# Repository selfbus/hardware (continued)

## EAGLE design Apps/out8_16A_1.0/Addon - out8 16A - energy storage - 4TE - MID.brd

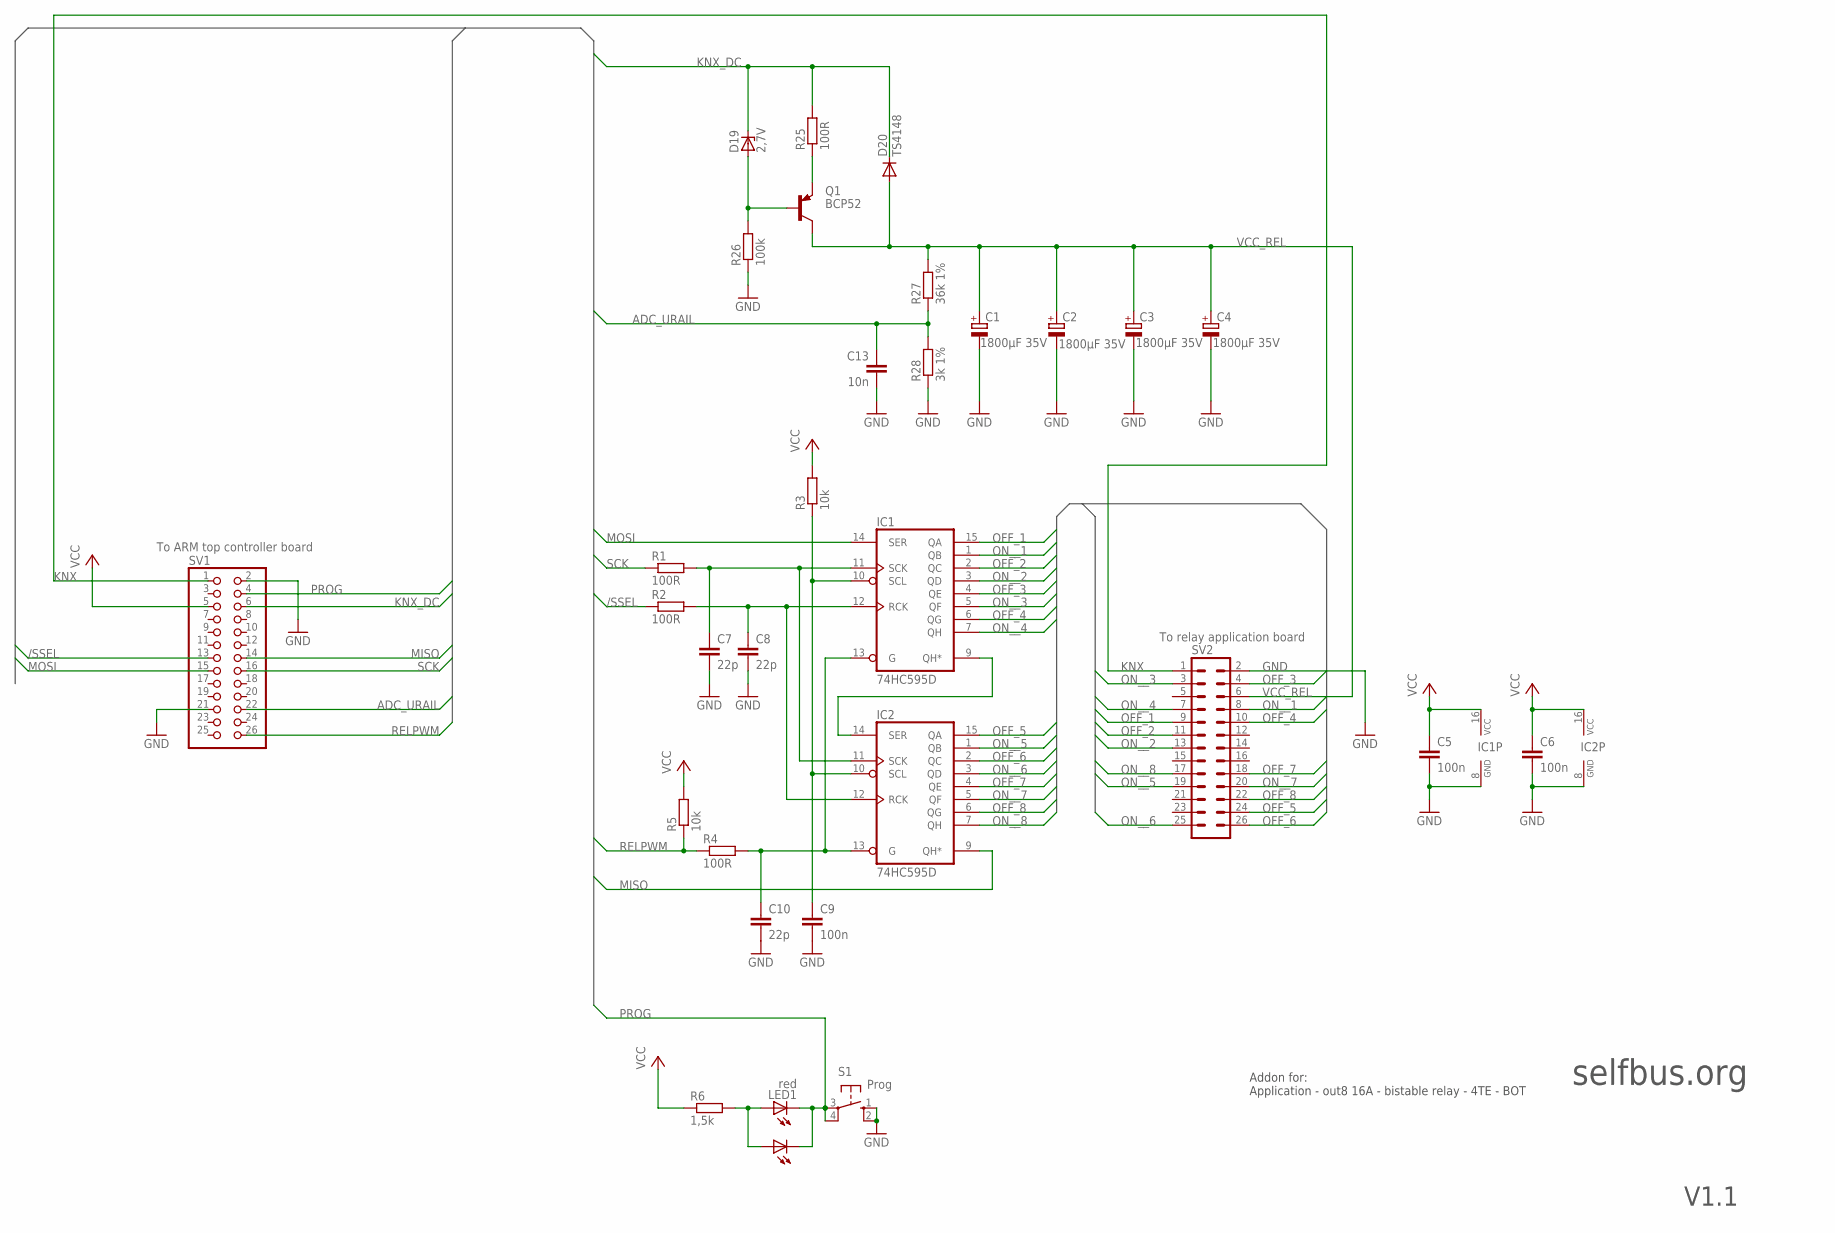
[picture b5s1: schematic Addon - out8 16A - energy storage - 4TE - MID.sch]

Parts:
C1, C2, C3, C4: 1800µF 35V; E5-13-30
C5, C6, C9: 100n; R0805M
C7, C8, C10: 22p; R0805M
C13: 10n; R0805M
D19: 2,7V; SOT23
D20: TS4148; D0805
IC1, IC2: 74HC595D; SO16
LED1: red; LED3MM
LED2: LG_T679-E1F1-1; PLCC2
Q1: BCP52; SOT223
R1, R2, R4, R25: 100R; R0805M
R3, R5: 10k; R0805M
R6: 1,5k; R0805M
R26: 100k; R0805M
R27: 36k 1%; R0805M
R28: 3k 1%; R0805M
S1: Prog; B3F-10XX
SV1: B; 2X13SMD
SV2: A; ML26

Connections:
/SSEL: R2.1, SV1.13
ADC_URAIL: C13.1, R27.1, R28.2, SV1.22
GND: C1.-, C2.-, C3.-, C4.-, C5.2, C6.2, C7.2, C8.2, C9.2, C10.2, C13.2, IC1.8 (GND), IC2.8 (GND), R26.1, R28.1, S1.1 (S), S1.2 (S1), SV1.2, SV1.21, SV2.2
KNX: SV1.1, SV2.1
KNX_DC: D19.3 (C), D20.C, R25.2, SV1.6
MISO: IC2.9 (QH*), SV1.14
MOSI: IC1.14 (SER), SV1.15
unnamed: D19.1 (A), Q1.1 (B), R26.2
unnamed: IC1.9 (QH*), IC2.14 (SER)
unnamed: C7.1, IC1.11 (SCK), IC2.11 (SCK), R1.2
unnamed: C8.1, IC1.12 (RCK), IC2.12 (RCK), R2.2
unnamed: LED1.A, LED2.A, R6.2
unnamed: Q1.3 (E), R25.1
unnamed: C10.1, IC1.13 (G), IC2.13 (G), R4.2
unnamed: C9.1, IC1.10 (SCL), IC2.10 (SCL), R3.1
OFF_1: IC1.15 (QA), SV2.9
OFF_2: IC1.2 (QC), SV2.11
OFF_3: IC1.4 (QE), SV2.4
OFF_4: IC1.6 (QG), SV2.10
OFF_5: IC2.15 (QA), SV2.24
OFF_6: IC2.2 (QC), SV2.26
OFF_7: IC2.4 (QE), SV2.18
OFF_8: IC2.6 (QG), SV2.22
ON__1: IC1.1 (QB), SV2.8
ON__2: IC1.3 (QD), SV2.13
ON__3: IC1.5 (QF), SV2.3
ON__4: IC1.7 (QH), SV2.7
ON__5: IC2.1 (QB), SV2.19
ON__6: IC2.3 (QD), SV2.25
ON__7: IC2.5 (QF), SV2.20
ON__8: IC2.7 (QH), SV2.17
PROG: LED1.K (C), LED2.C, S1.3, S1.4 (P1), SV1.4
RELPWM: R4.1, R5.1, SV1.26
SCK: R1.1, SV1.16
VCC: C5.1, C6.1, IC1.16 (VCC), IC2.16 (VCC), R3.2, R5.2, R6.1, SV1.5
VCC_REL: C1.+, C2.+, C3.+, C4.+, D20.A, Q1.2 (C), Q1.4 (C), R27.2, SV2.6

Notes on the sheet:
To ARM top controller board
To relay application board
V1.1
selfbus.org
Addon for: Application - out8 16A - bistable relay - 4TE - BOT

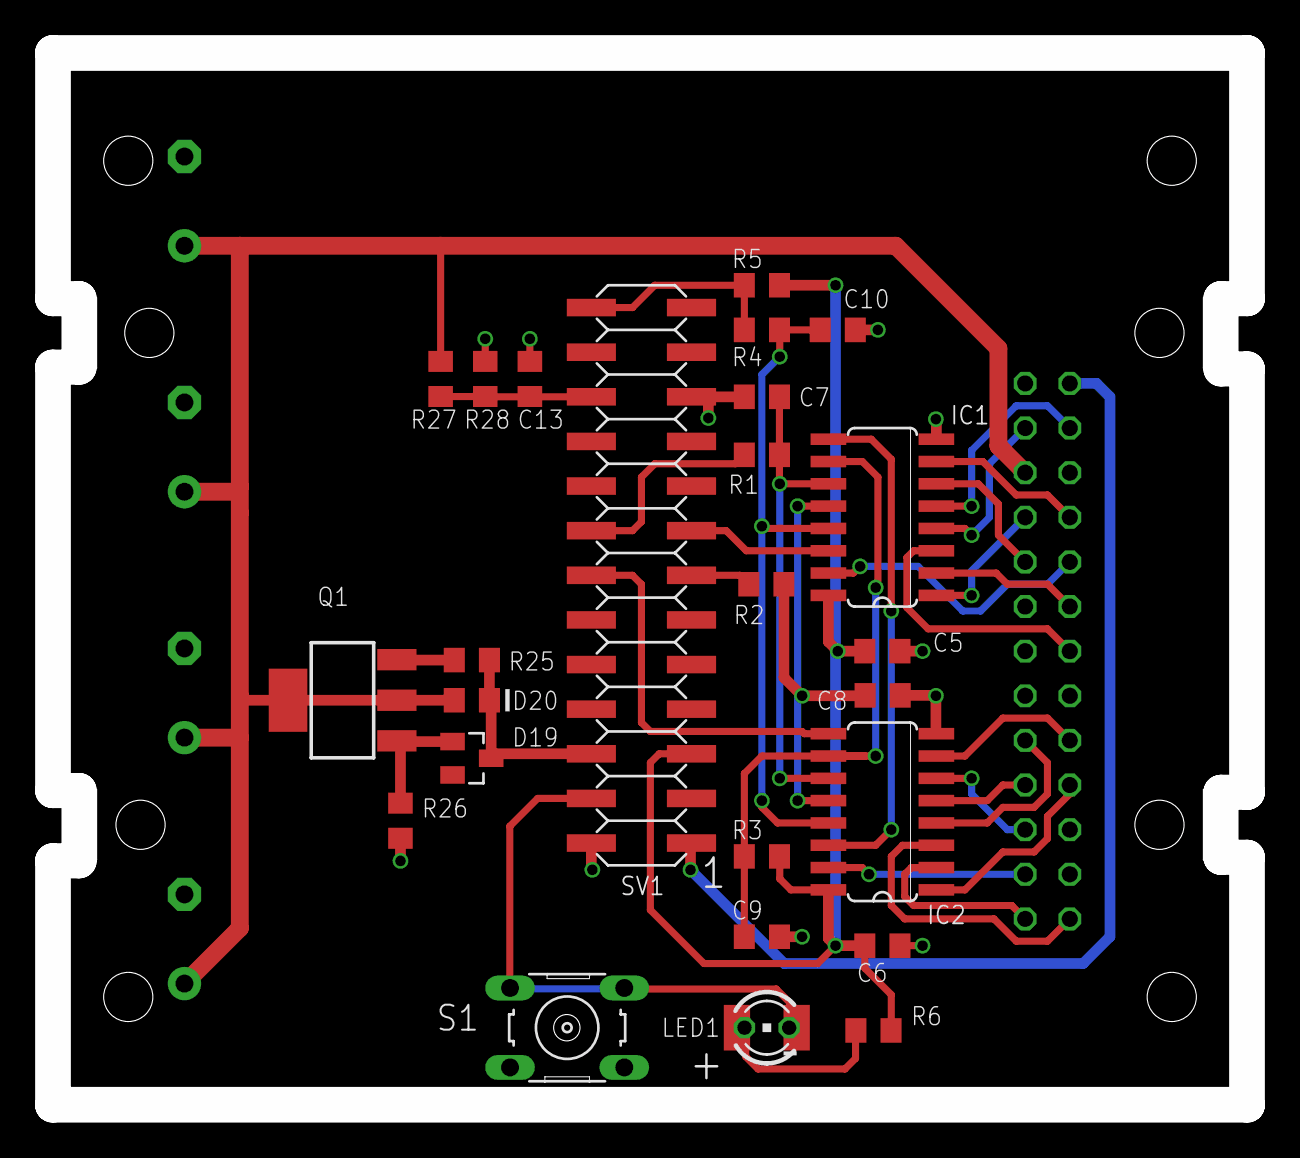
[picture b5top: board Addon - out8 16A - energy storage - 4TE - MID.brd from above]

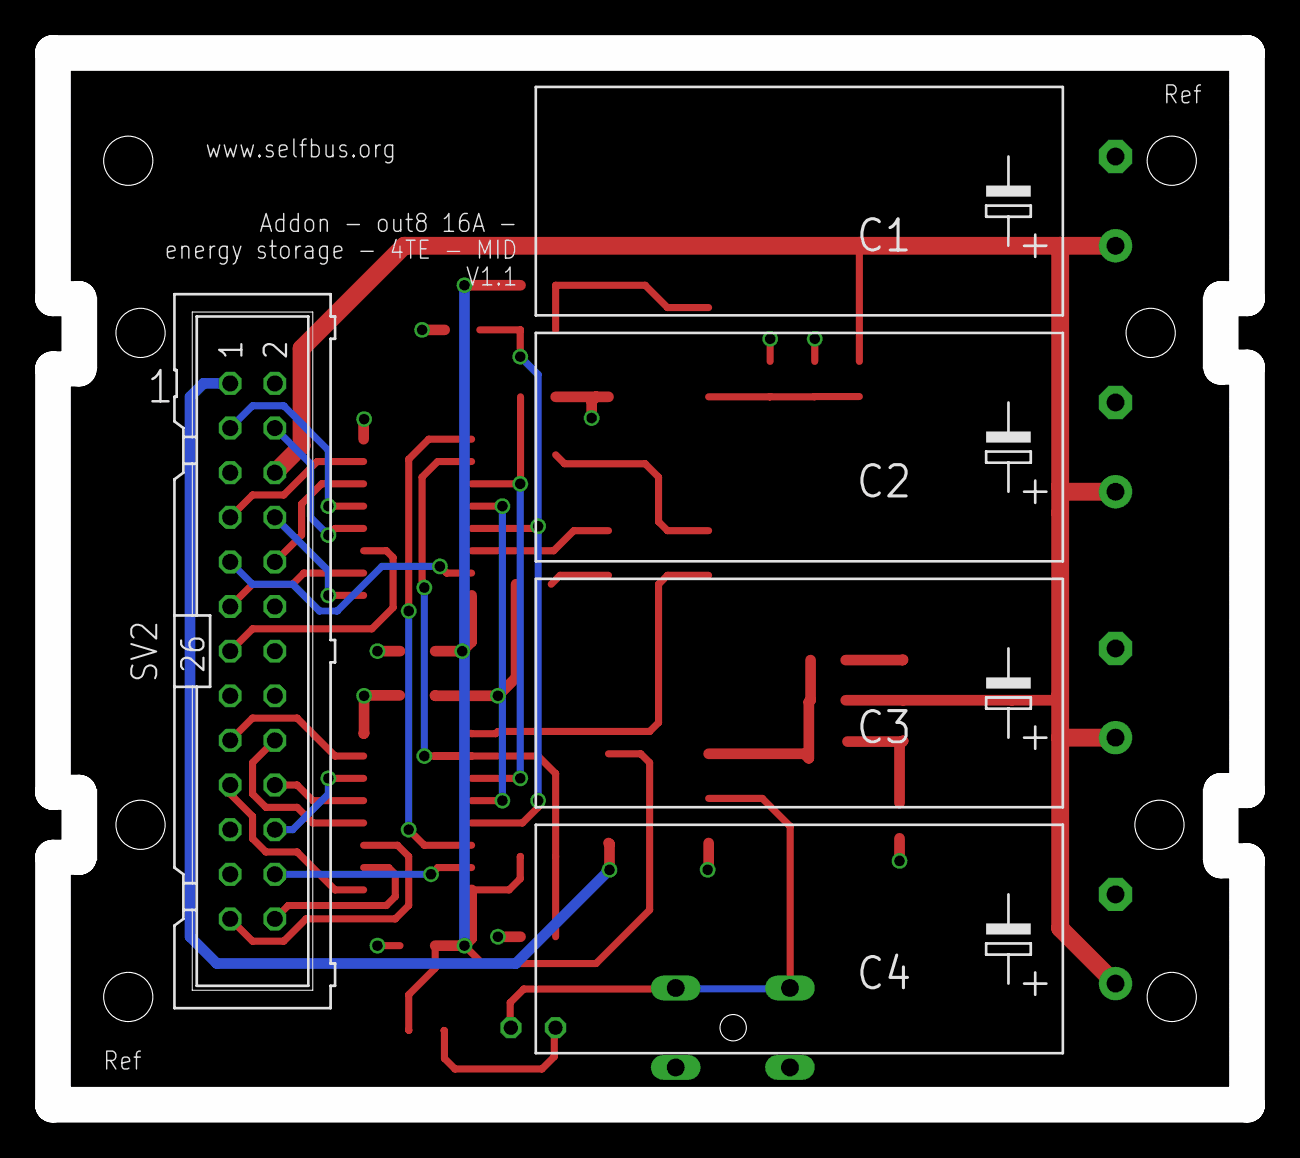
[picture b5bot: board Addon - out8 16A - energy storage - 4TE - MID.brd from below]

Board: 2 copper layers, 68.0 x 59.9 mm, 31 parts (5 on the bottom side), 36 nets.

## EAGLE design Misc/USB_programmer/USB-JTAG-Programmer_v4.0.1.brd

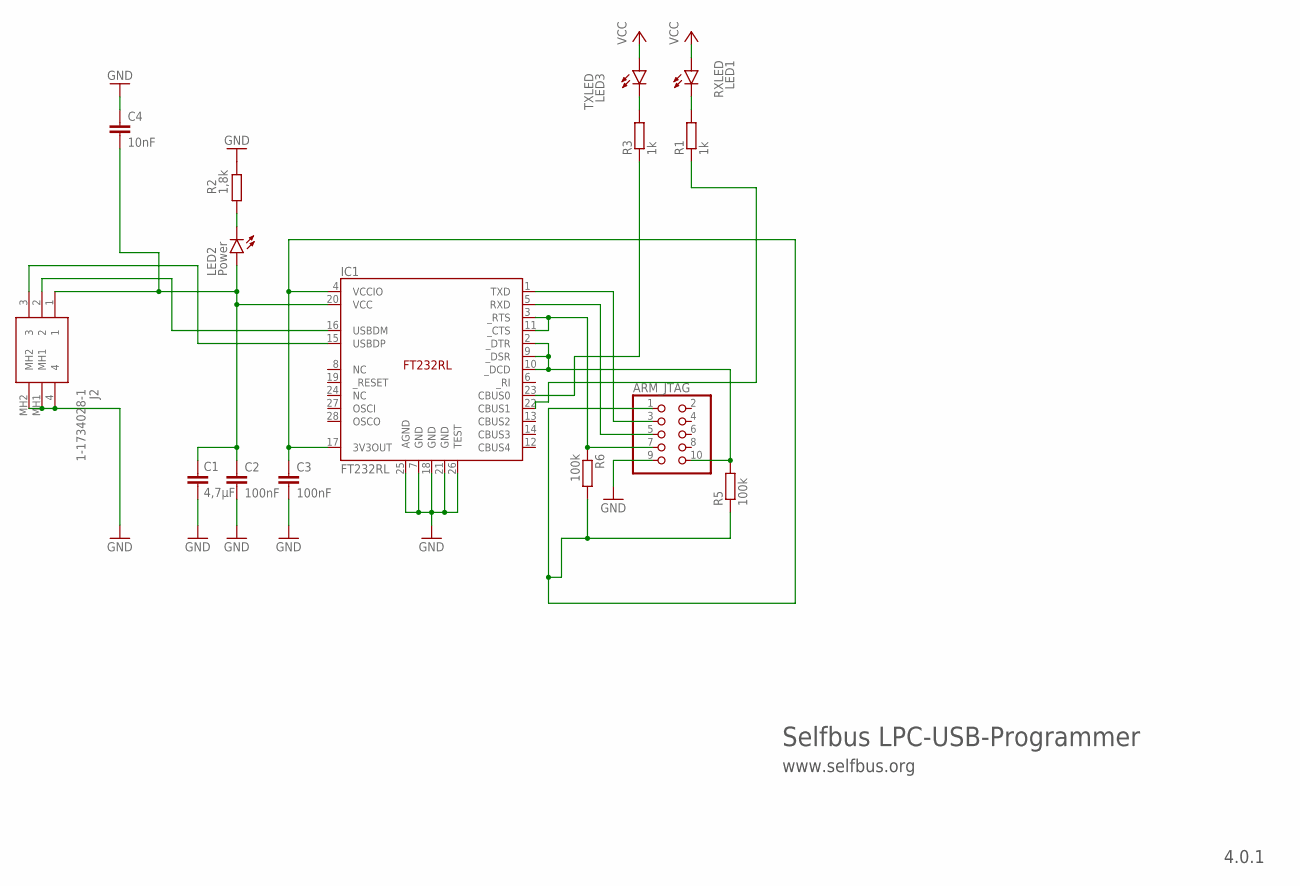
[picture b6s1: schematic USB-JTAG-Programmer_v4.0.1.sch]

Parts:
ARM_JTAG: PINHD-2X5_2.00; 2X05M
C1: 4,7µF; C1206K
C2, C3: 100nF; C0805K
C4: 10nF; C0805K
IC1: FT232RL; SSOP-28
J2: 1-1734028-1; 117340281
LED1: RXLED; CHIPLED_0805
LED2: Power; CHIPLED_0805
LED3: TXLED; CHIPLED_0805
R1, R3: 1k; R0805
R2: 1,8k; R0805
R5, R6: 100k; R0805

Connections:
CBUS0: IC1.23 (CBUS0), R3.1
GND: ARM_JTAG.9, C1.2, C2.2, C3.2, C4.1, IC1.7 (GND), IC1.18 (GND), IC1.21 (GND), IC1.25 (AGND), IC1.26 (TEST), J2.4, J2.MH1, J2.MH2, R2.2
unnamed: LED2.C, R2.1
unnamed: LED3.C, R3.2
unnamed: IC1.22 (CBUS1), R1.1
unnamed: LED1.C, R1.2
PROG_PWR_ON: ARM_JTAG.10, IC1.2 (_DTR), IC1.9 (_DSR), IC1.10 (_DCD), R5.2
RTS_CTS1: ARM_JTAG.7, IC1.3 (_RTS), IC1.11 (_CTS), R6.1
RXD: ARM_JTAG.5, IC1.5 (RXD)
TXD: ARM_JTAG.3, IC1.1 (TXD)
USBDM: IC1.16 (USBDM), J2.2
USBDP: IC1.15 (USBDP), J2.3
VCC: C1.1, C2.1, C4.2, IC1.20 (VCC), J2.1, LED1.A, LED2.A, LED3.A
VCCIO: ARM_JTAG.1, C3.1, IC1.4 (VCCIO), IC1.17 (3V3OUT), R5.1, R6.2

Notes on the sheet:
Selfbus LPC-USB-Programmer
www.selfbus.org
4.0.1

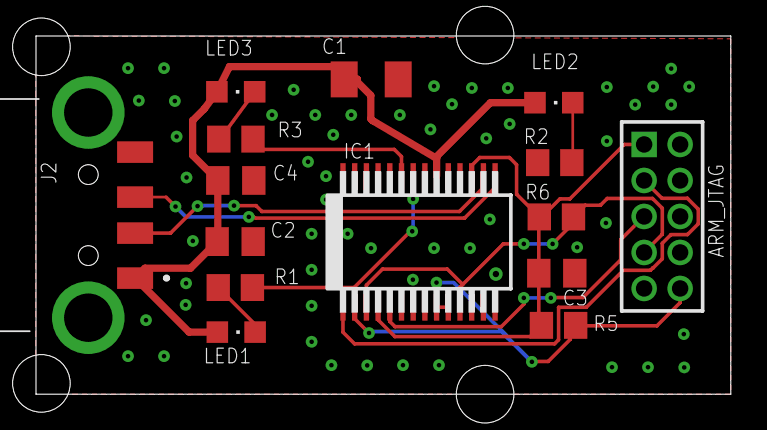
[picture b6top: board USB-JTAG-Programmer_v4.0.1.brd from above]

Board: 2 copper layers, 38.6 x 19.9 mm, 15 parts (0 on the bottom side), 14 nets.

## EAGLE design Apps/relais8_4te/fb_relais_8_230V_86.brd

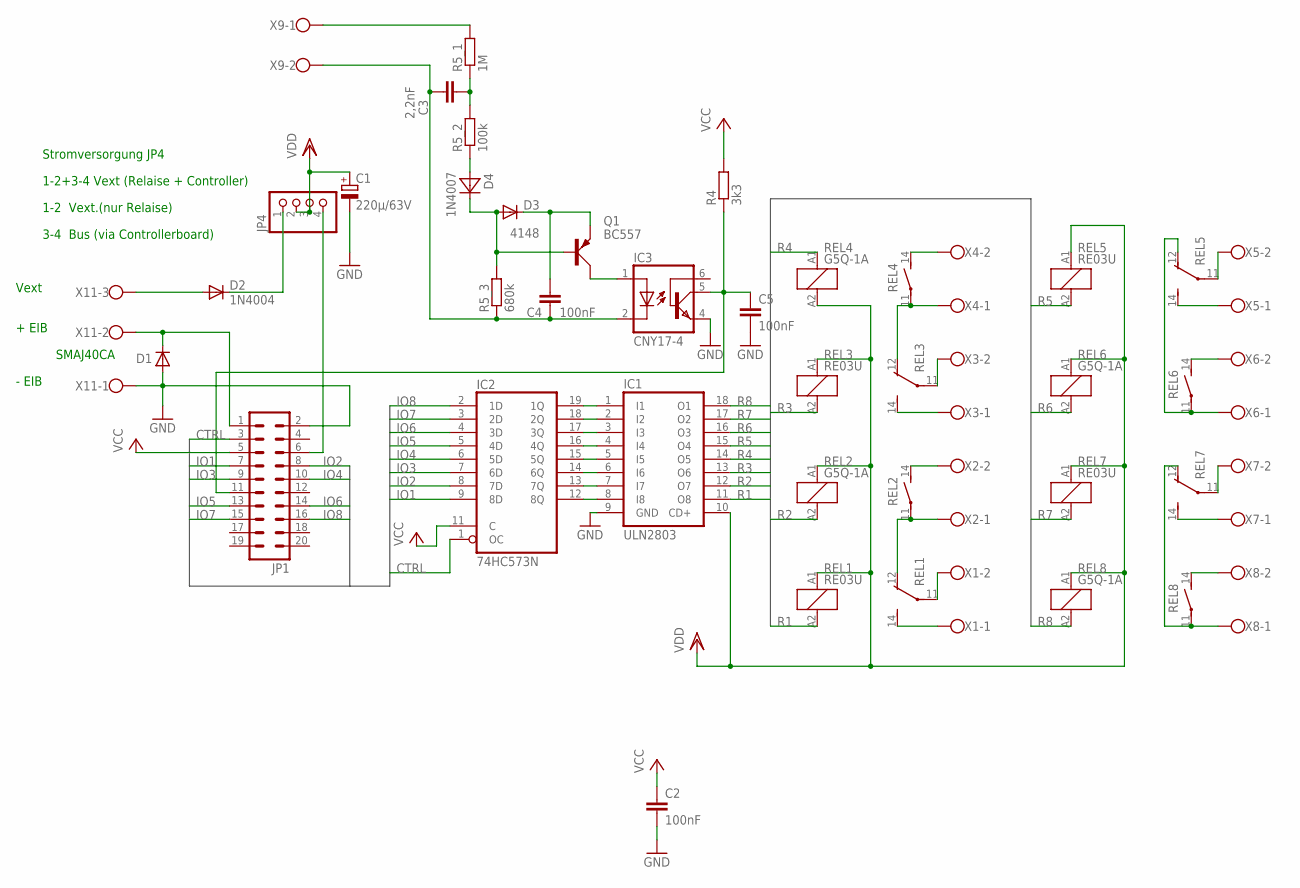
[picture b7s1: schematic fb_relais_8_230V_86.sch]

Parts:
C1: 220µ/63V; E5-10,5
C2, C4, C5: 100nF; C050-024X044
C3: 2,2nF; C102-043X133
D1: D-SMB; SMB
D2: 1N4004; DO41-10
D3: 4148; D-2.5
D4: 1N4007; DO41-7
IC1: ULN2803; DIL18
IC2: 74HC573N; DIL20
IC3: CNY17-4; DIL06
JP1: ML20
JP4: PINHD-1X4; 1X04
Q1: BC557; SOT54A
R4: 3k3; 0207/7
R5_1: 1M; 0207/7
R5_2: 100k; 0207/7
R5_3: 680k; 0207/7
REL1, REL3, REL5, REL7: RE03U; G5Q_1_EU
REL2, REL4, REL6, REL8: G5Q-1A; RE-SCHRACK
X1, X2, X3, X4, X5, X6, X7, X8, X9: W237-102
X11: W237-3E

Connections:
CTRL: IC2.1 (OC), JP1.3
GND: C1.-, C2.2, C5.2, D1.2 (A), IC1.9 (GND), IC2.10 (GND), IC3.4 (EMI), JP1.2, X11.1
IO1: IC2.9 (8D), JP1.7
IO2: IC2.8 (7D), JP1.8
IO3: IC2.7 (6D), JP1.9
IO4: IC2.6 (5D), JP1.10
IO5: IC2.5 (4D), JP1.13
IO6: IC2.4 (3D), JP1.14
IO7: IC2.3 (2D), JP1.15
IO8: IC2.2 (1D), JP1.16
unnamed: REL2.14 (S), X2.2
unnamed: REL3.12 (O), REL4.11, X4.1
unnamed: REL3.14 (S), X3.1
unnamed: REL3.11, X3.2
unnamed: REL8.14 (S), X8.2
unnamed: REL1.12 (O), REL2.11, X2.1
unnamed: REL1.14 (S), X1.1
unnamed: REL1.11, X1.2
unnamed: REL5.12 (O), REL6.11, X6.1
unnamed: REL5.14 (S), X5.1
unnamed: REL7.11, X7.2
unnamed: REL6.14 (S), X6.2
unnamed: REL5.11, X5.2
unnamed: D2.A, X11.3
unnamed: REL7.14 (S), X7.1
unnamed: R5_1.2, X9.1
unnamed: D4.A, R5_2.1
unnamed: REL7.12 (O), REL8.11, X8.1
unnamed: D1.1 (C), JP1.1, X11.2
unnamed: D2.C, JP4.1
unnamed: IC3.1 (A), Q1.C
unnamed: C4.2, D3.C, Q1.E
unnamed: JP1.6, JP4.4
unnamed: IC1.1 (I1), IC2.19 (1Q)
unnamed: IC1.2 (I2), IC2.18 (2Q)
unnamed: IC1.3 (I3), IC2.17 (3Q)
unnamed: IC1.4 (I4), IC2.16 (4Q)
unnamed: IC1.5 (I5), IC2.15 (5Q)
unnamed: IC1.6 (I6), IC2.14 (6Q)
unnamed: IC1.7 (I7), IC2.13 (7Q)
unnamed: IC1.8 (I8), IC2.12 (8Q)
unnamed: REL4.14 (S), X4.2
unnamed: C3.2, C4.1, IC3.2 (C), R5_3.1, X9.2
unnamed: D3.A, D4.C, Q1.B, R5_3.2
unnamed: C5.1, IC3.5 (COL), JP1.11, R4.1
unnamed: C3.1, R5_1.1, R5_2.2
R1: IC1.11 (O8), REL1.A2 (2)
R2: IC1.12 (O7), REL2.A2 (2)
R3: IC1.13 (O6), REL3.A2 (2)
R4: IC1.14 (O5), REL4.A1 (1)
R5: IC1.15 (O4), REL5.A2 (2)
R6: IC1.16 (O3), REL6.A2 (2)
R7: IC1.17 (O2), REL7.A2 (2)
R8: IC1.18 (O1), REL8.A2 (2)
VCC: C2.1, IC2.11 (C), IC2.20 (VCC), JP1.5, R4.2
VDD: C1.+, IC1.10 (CD+), JP4.2, JP4.3, REL1.A1 (1), REL2.A1 (1), REL3.A1 (1), REL4.A2 (2), REL5.A1 (1), REL6.A1 (1), REL7.A1 (1), REL8.A1 (1)

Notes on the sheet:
+ EIB
- EIB
Vext
1-2 Vext.(nur Relaise)
3-4 Bus (via Controllerboard)
Stromversorgung JP4
SMAJ40CA
1-2+3-4 Vext (Relaise + Controller)

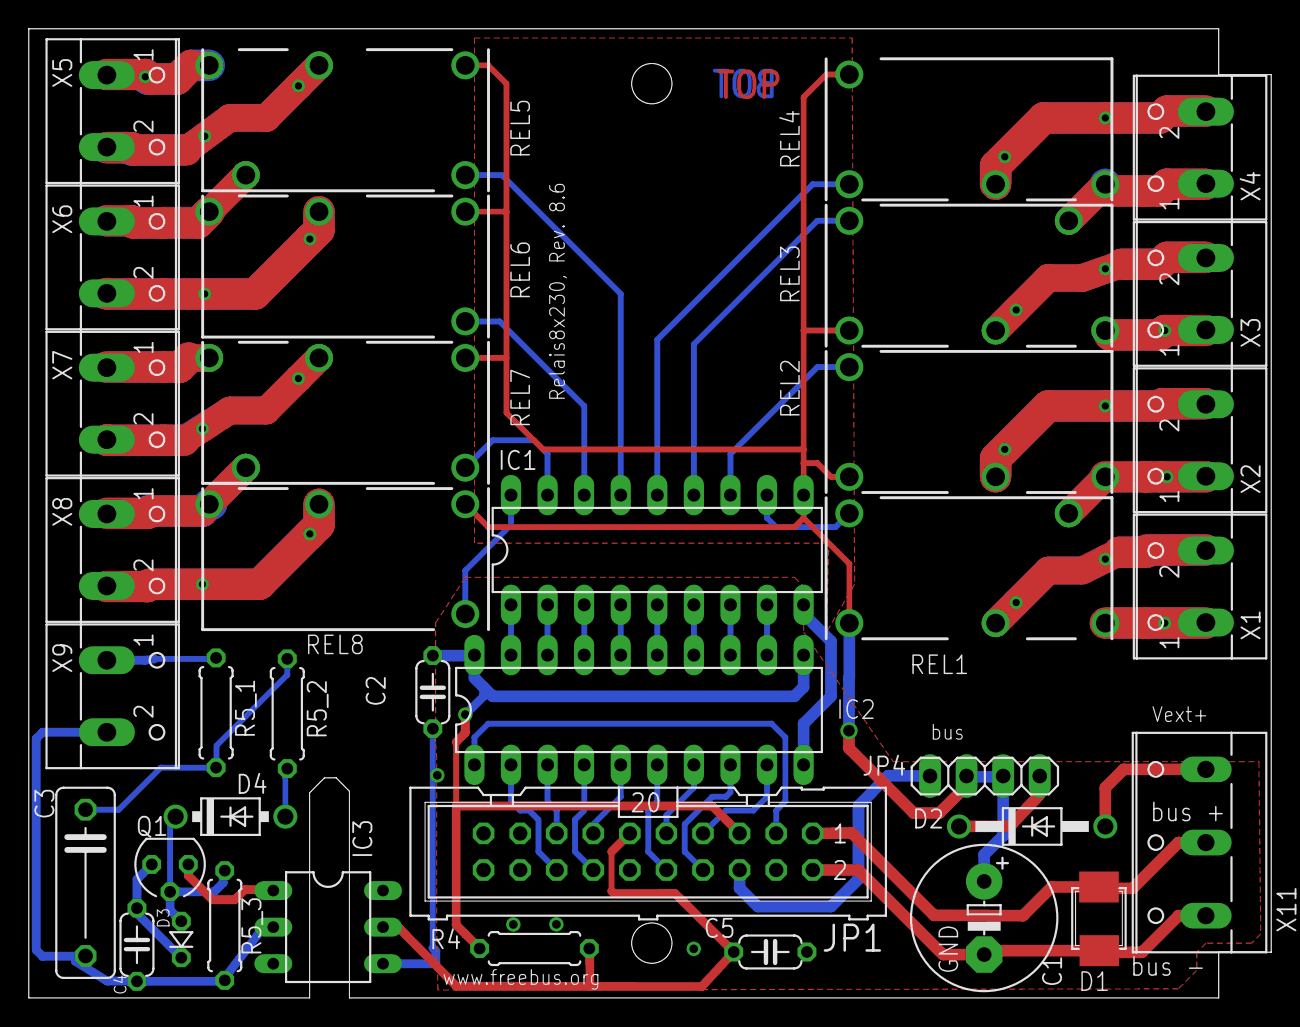
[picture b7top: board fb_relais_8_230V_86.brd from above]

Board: 2 copper layers, 86.3 x 67.3 mm, 37 parts (0 on the bottom side), 56 nets.

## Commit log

2012-12-12 controller2TE in ordner controller verschoben
2012-12-12 first upload
2012-12-12 app-dev in misc verschoben
2012-12-12 .svn dateien entfernt
2012-12-12 Lötnägel zugefügt
2012-12-31 v02: Randbahnen nach top verlegt und dimension angepasst
2012-12-31 neue dimension
2013-02-27 Release der unsymmetrischen Drossel 2TE
2013-02-27 Release der asymmetrischen 2TE Drossel
2013-04-11 Touch sensor für erikdc hinzugefügt.
2013-04-29 first upload new out8 zerodetect
2013-05-13 first upload out8_16A_1.0
2013-05-14 rename
2013-05-25 Moved lpc922_4te controller from hardware-incubation to here, Added .gitignore for temp Eagle files
2013-05-25 Renamed controller to Controller, described top level directories in the README.md
2013-05-25 Described top level directories in the README.md
2013-05-25 Updated the README.md file
2013-06-08 Rauchmelder verschoben von hardware-incubation
2013-06-13 move to hardware misc
2013-06-18 Added fan speed controller
2013-08-18 neue version, mit Bus spannungs ausfall erkennung
2013-10-01 ssr8_4te moved to hardware-incubation/Apps
2013-10-11 UPModule von hardware-incubation hier her verschoben
2013-11-10 Dateien umbenannt damit sie zu den alten Dateien passen.
2013-11-11 Neu: Raumthermostat ERT30, mit Erlaubnis von mel01
2013-11-15 stuetzspannung gefixt
2013-11-15 Bezeichnung korrigiert.
2013-11-16 update Busagi
2013-11-16 update rmgira
2013-11-16 Alte Version 2.1 wieder hinzugefügt
2014-01-21 Beschriftung korrigiert.
2014-02-15 Initial release of EIB_LCD hardware
    This release contains V1.1 of the EIB_LCD hardware.
    The LCD base board is designed with Target 3001! V12.
2014-02-16 Pin assignment report for Xilinx
2014-05-20 LPC Programmer v3.7 mit ARM JTAG Pinhead
2014-06-12 Loetjumper fuer die Taster MUX Leitung eingefuegt
2014-12-13 TS_DIL mit EIB Klemme, TS_SMD 2.00 mit EIB-Klemme
2015-02-19 Taster 4fach: 3D-Print for the protection cup. THX to Vincent!
2015-03-05 kleine Änderung an der Klemme und diode dahinter
2015-03-24 VCC zugefügt für ARM + LPC
2015-04-09 Rauchmelder in smd, neue Position der Wagoklemme
2015-04-10 Kosmetik am Rauchmelder 2.2
2015-04-11 RM2.2, cleanup, checked power supply
2015-04-14 Kosmetik am Rauchmelder 2.2A.brd
2015-04-14 RM 2.2C, kleinigkeiten am Layout gefixt. Kondensator verschoben.
2015-04-14 RM2.2C, add some GND Vias
2015-04-15 kosmetik am silk
2015-04-16 Passmarken-vias zugefügt
2015-04-16 TS-smd 2.00
2015-05-19 update produktions stand.
2015-12-03 BUGFIX LED7
2016-06-04 The new 8 out 16A V2 and v2.1 bugfix footprint uln2803
2017-02-01 version mir aussparung
2017-02-01 pullup für zero-detect-ARM zugefügt.
2020-02-15 Gehäusebeschriftung hinzugefügt
2020-10-31 KNX Klemmen Polarität vertauscht
2020-11-25 Hint for usage of R2 added.
2021-03-15 Added new very small USB-JTAG progger for ARM µC flashing
    Added v1.0 of a new (very small) USB-JTAG progger. This one can *not* be used for LPC922 flashig but only for our ARM µC flashing. Fits into some USB stick cases.
2021-05-01 deleted old .svn folder
2022-03-22 [Progger] - removed overlaps, added version labels
2022-03-22 [BB Pwr+KNX] - added breakout board for power supply and KNX connection
    file is named 1.0.0 but this is still WIP will still remain on dev until stability was proven!
2022-03-22 README.md updated
2022-04-08 [IOmodule8xUP] -initial commit
    version is quite stable. Some re-arrangement neccessary due to changes in corresponding Pwr+KNX-BB
2022-04-08 [IOmodule8xUP] moved power supply pins and SWD connector
    consequences of changes in breakout board
2022-04-08 [IOmodule8xUP] added holes / change BB-fixing-pins from 4 to 2
2022-04-21 [IOmodule8xUP] added JST ZH connector for I2C; reordered
2022-04-21 [IOmodule8xUP] massive re-arrangement
    divided part so that 4 IOs are on TOP and 4 IOs on BOT
2022-04-22 [IOmodule8xUP] optimized names & values positions; changed JP1 to 2mm
2022-04-22 [IOmodule8xUP] optimized holes and markers; added vias;
2022-04-22 [IOmodule8xUP] vias added, Z-Diode Value changed
2022-04-22 [IOmodule8xUP] added 100R resistor to each IO
    Protection of potential mess with 3V3 Z-Diodes when ARM pins run in high mode
2022-04-22 [IOmodule8xUP] added values of 100R resistors; optimized routing
2022-04-22 [IOmodule8xUP] moved ISP parts closer to PCB edge
2022-04-24 [IOmodule8xUP] added SPI footprint to SSEL0
2022-04-24 [IOmodule8xUP] fixed errors with SPI routing
2022-04-25 [IOmodule8xUP] several errors fixed - see detailed message
    switch to MISO1/MOSI1 with SCK1
    changed order of TVS3 and SWD components
    fixed unconnected +3V3 pin at SWD header
    fixed width of THT holes for prog button
    connected pin 3 and 7 of IC2 to +3V3 so that also a flash IC could beused
2022-04-25 [IOmodule8xUP] added debug RXD / TXD / GND solder pads
2022-04-26 [IOmodule8xUP] added missing blocking capacitor to IC2
2022-04-26 [IOmodule8xUP] added labels on PCB
2022-05-02 Terminal [BB Pwr+KNX] - renamed files to contain no version information
2022-05-02 added Addon - out8 16A - energy storage - 4TE - MID - V1.1
2022-05-02 renamed out8-V2 --> Application - out8 16A - bistable relay - 4TE - BOT
2022-05-02 renamed out8-V2.1 --> Application - out8 16A - bistable relay - 4TE - BOT
2022-05-02 updated Application - out8 16A - bistable relay - 4TE - BOT - V2.2; added SJ2 for use with addon - energy storage; opütimized silkscreen and relaypositions
2022-05-04 C5 entfernt Polygone eingefügt
2022-05-20 [out8 16A bistable] Renamed / moved directory
2022-05-20 Revert "[out8 16A bistable] Renamed / moved directory"
    This reverts commit 9322f3d7384a47aca0304cc67b30624836ee4082.
2022-05-22 [Application - out8 16A - bistable relay - 4TE - BOT] erc edited
2022-11-15 [out8_16A] added interactive BOM's
2022-11-28 [lpc_2te] fixed lpc922 package in board
2022-11-30 [BB_Pwr+KNX] - removed v-split at buck's enable pin
2022-11-30 [LedTaster_4te] added interactive BOM and LED positioner
2022-12-15 [IOmodule8xUP] - some minor optimizations
    corrected mixed up SWDIO / SWCLK labels
    optimized some vias
    optimized schematic
    added ferrite values
2023-01-23 [out8] 20mm standoff between energy storage and 4TE top-controller PCB
2023-02-01 [IOmodule8xUP] - breaking change of routing, I2C optimization
    re-routed some IOs to other ARM pins
    added 2nd alternative to connect I2C peripherals
2023-02-02 [BB_Pwr+KNX] removed attributes, switched to 2x47uF mlccs
2023-02-08 [BB_Pwr+KNX] - changed values to standard values
2023-02-08 [IOmodule8xUP] - changed values to standard values
2023-02-09 [BB_Pwr+KNX] - update pin positions
    accidentially committed a version with old pin positions yesterday
2023-03-15 [IOmodule8xFM] parts re-arranged; pin assignement of I2C conn. corrected
2023-03-15 [BB_Pwr+KNX] - updated docu; updated values of buck components
2023-03-15 Readme change reverted
2023-03-17 [BB_Pwr+KNX] - widened holes for power inductor
2023-03-22 [BB_Pwr+KNX] - rearranged parts, reduced heat dissipation pins to 2
    rearrangement in order to avoid by accident wrongly placed parts and connected pin headers
2023-03-22 [BB_Pwr+KNX] - labels rearranged; MLCC values updated
2023-03-25 [BB_Pwr+KNX] - rearranged parts colliding with IO module
2023-04-04 [IOmodule8xFM] - switched RX / TX to 2,54 pin header added status LED
2023-04-18 [IOmodule8xFM] - moved MLCC to avoid collision with EIB pin of power PCB
2023-05-11 Update README.md before archiving "hardware" repo
